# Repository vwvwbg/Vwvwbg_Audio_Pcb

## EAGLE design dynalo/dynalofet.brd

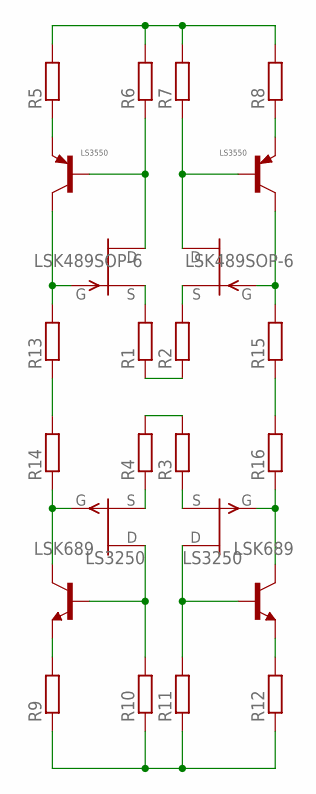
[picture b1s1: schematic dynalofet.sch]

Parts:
Q1: LS3250; SOT-23-6
Q2: LS3550; SOT-23-6
Q3: LSK489SOP-6; SOT-23-6
Q4: LSK689; SOT-23-6
R1, R2, R3, R4, R5, R6, R7, R8, R9, R10, R11, R12, R13, R14, R15, R16: R-EU_MELF0204W; MINI_MELF-0204W

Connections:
unnamed: Q2.3 (B), Q3.5 (D), R6.1
unnamed: Q2.4 (C), Q3.4 (G), R13.2
unnamed: Q2.1 (B), Q3.2 (D), R7.1
unnamed: Q2.6 (C), Q3.1 (G), R15.2
unnamed: Q1.4 (C), Q4.4 (G), R14.1
unnamed: Q1.3 (B), Q4.5 (D), R10.2
unnamed: Q1.1 (B), Q4.2 (D), R11.2
unnamed: Q1.6 (C), Q4.1 (G), R16.1
unnamed: Q4.3 (S), R3.1
unnamed: Q4.6 (S), R4.1
unnamed: Q3.6 (S), R1.2
unnamed: Q3.3 (S), R2.2
unnamed: R1.1, R2.1
unnamed: R3.2, R4.2
unnamed: R5.2, R6.2, R7.2, R8.2
unnamed: Q2.5 (E), R8.1
unnamed: Q2.2 (E), R5.1
unnamed: Q1.2 (E), R9.2
unnamed: Q1.5 (E), R12.2
unnamed: R9.1, R10.1, R11.1, R12.1
unnamed: R13.1, R14.2
unnamed: R15.1, R16.2

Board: 2 copper layers, 20 parts (0 on the bottom side), 22 nets, no tracks yet.

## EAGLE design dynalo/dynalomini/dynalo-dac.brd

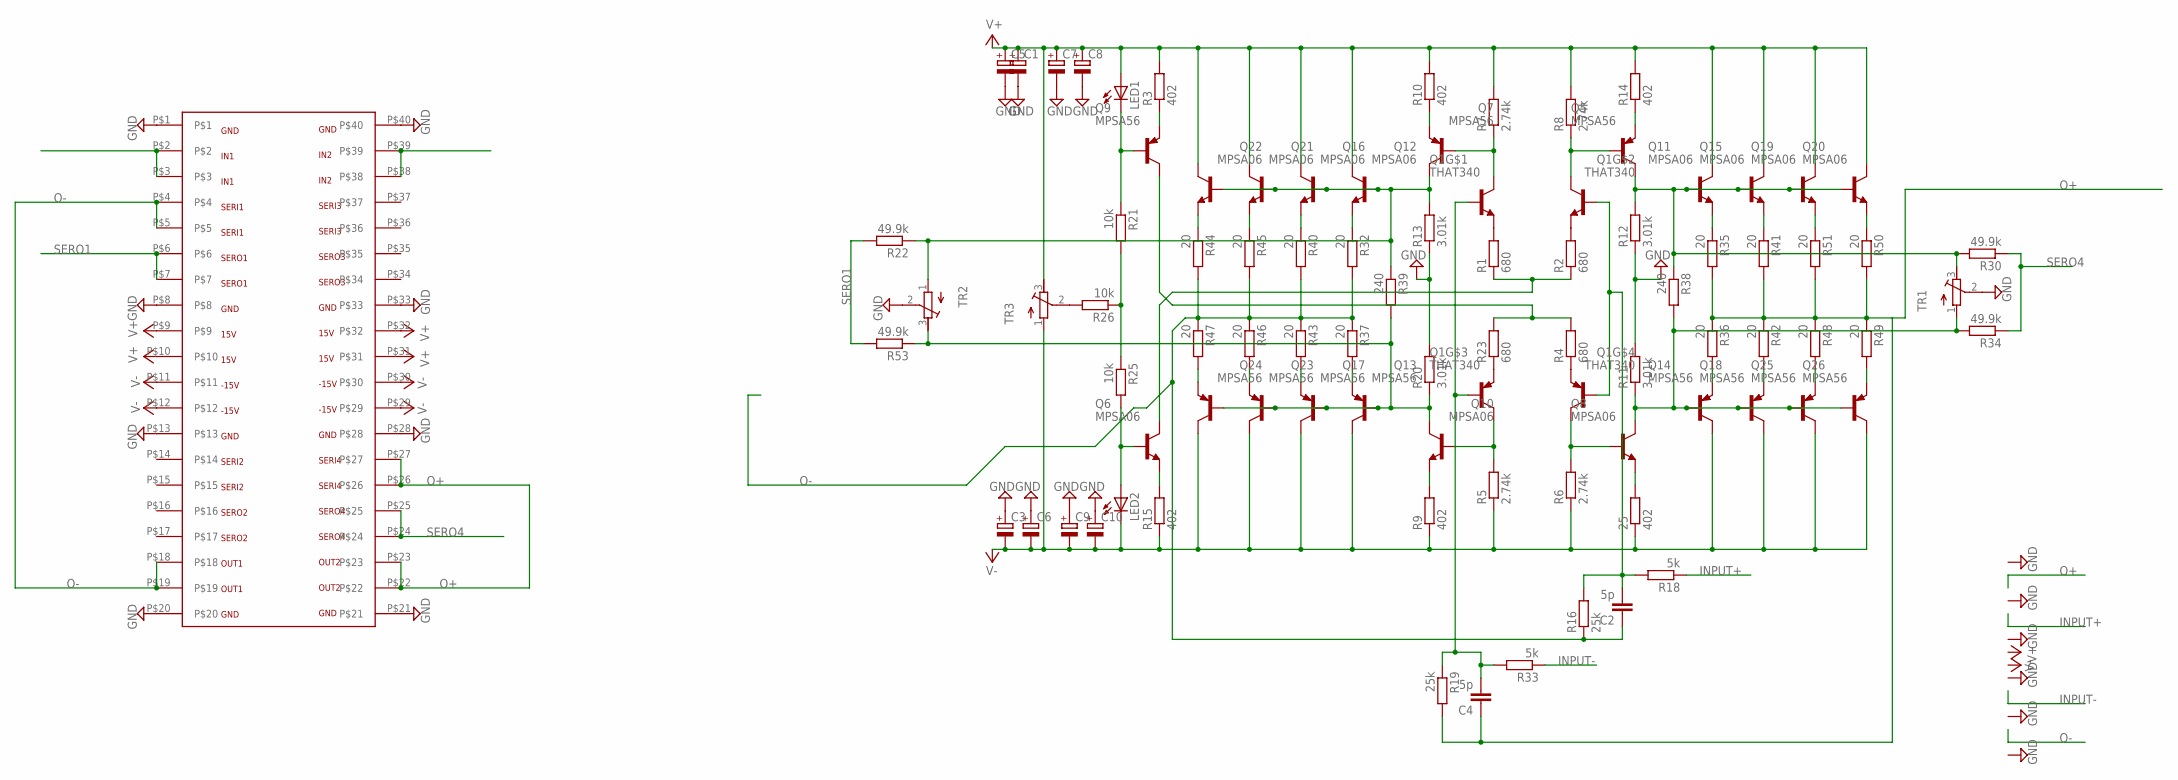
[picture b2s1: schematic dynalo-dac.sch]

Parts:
25: 402; MINI_MELF-0204W
C1, C3, C5, C6, C7, C8, C9, C10: CPOL-EUSP-CAP-CX; SP-CAP-CX
C2, C4: 5p; C0805
LED1, LED2: LED5MM
Q1: THAT340; DIP254P762X510-14
Q5, Q7, Q9, Q13, Q14, Q17, Q18, Q23, Q24, Q25, Q26: MPSA56; TO92-BCE
Q6, Q8, Q10, Q11, Q12, Q15, Q16, Q19, Q20, Q21, Q22: MPSA06; TO92-1
R1, R2, R4, R23: 680; MINI_MELF-0204W
R3, R9, R10, R14, R15: 402; MINI_MELF-0204W
R5, R6, R7, R8: 2.74k; MINI_MELF-0204W
R11, R12, R13, R20: 3.01k; MINI_MELF-0204W
R16, R19: 25k; MINI_MELF-0204W
R18, R33: 5k; MINI_MELF-0204W
R21, R25, R26: 10k; MINI_MELF-0204W
R22, R30, R34, R53: 49.9k; MINI_MELF-0204W
R32, R35, R36, R37, R40, R41, R42, R43, R44, R45, R46, R47, R48, R49, R50, R51: 20; MINI_MELF-0204W
R38, R39: 240; MINI_MELF-0204W
TR1, TR2, TR3: R-TRIMM3296W; RTRIM3296W
U$1: VDACA

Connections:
GND: C1.-, C3.+, C5.-, C6.+, C7.-, C8.-, C9.+, C10.+, R11.2, R12.1, R13.1, R20.2, TR1.2 (S), TR2.2 (S), U$1.P$1, U$1.P$8, U$1.P$13, U$1.P$20, U$1.P$21, U$1.P$28, U$1.P$33, U$1.P$40
INPUT+: R18.1, U$1.P$38, U$1.P$39
INPUT-: R33.1, U$1.P$2, U$1.P$3
unnamed: Q1.3 (E), R1.2
unnamed: Q1.12 (E), R2.2
unnamed: Q1.5 (E), R23.1
unnamed: Q1.10 (E), R4.1
unnamed: Q1.1 (C), Q7.C (B), R7.1
unnamed: Q1.14 (C), Q5.C (B), R8.1
unnamed: Q1.7 (C), Q10.2 (B), R5.2
unnamed: Q1.8 (C), Q8.2 (B), R6.2
unnamed: Q9.B (C), R4.2, R23.2
unnamed: Q6.3 (C), R1.1, R2.1
unnamed: Q10.1 (E), R9.2
unnamed: Q7.E, R10.1
unnamed: C4.2, Q1.2 (B), Q1.6 (B), R19.1, R33.2
unnamed: C2.2, Q1.9 (B), Q1.13 (B), R16.2, R18.2
unnamed: Q7.B (C), Q12.2 (B), Q16.2 (B), Q21.2 (B), Q22.2 (B), R13.2, R22.1, R39.1, TR2.1 (A)
unnamed: Q10.3 (C), Q13.C (B), Q17.C (B), Q23.C (B), Q24.C (B), R20.1, R39.2, R53.1, TR2.3 (E)
unnamed: Q11.1 (E), R35.1
unnamed: Q5.B (C), Q11.2 (B), Q15.2 (B), Q19.2 (B), Q20.2 (B), R12.2, R30.2, R38.1, TR1.3 (E)
unnamed: 25.2, Q8.1 (E)
unnamed: Q14.E, R36.2
unnamed: Q5.E, R14.1
unnamed: Q9.E, R3.1
unnamed: Q6.1 (E), R15.2
unnamed: Q18.E, R42.2
unnamed: Q15.1 (E), R41.1
unnamed: Q19.1 (E), R51.1
unnamed: Q20.1 (E), R50.1
unnamed: Q25.E, R48.2
unnamed: Q8.3 (C), Q14.C (B), Q18.C (B), Q25.C (B), Q26.C (B), R11.1, R34.2, R38.2, TR1.1 (A)
unnamed: Q26.E, R49.2
unnamed: R26.2, TR3.2 (S)
unnamed: R21.2, R25.1, R26.1
unnamed: Q22.1 (E), R44.1
unnamed: Q21.1 (E), R45.1
unnamed: Q16.1 (E), R40.1
unnamed: Q12.1 (E), R32.1
unnamed: Q24.E, R47.2
unnamed: Q23.E, R46.2
unnamed: Q17.E, R43.2
unnamed: Q13.E, R37.2
unnamed: LED2.A, Q6.2 (B), R25.2
unnamed: LED1.K (C), Q9.C (B), R21.1
O+: C4.1, R19.2, R35.2, R36.1, R41.2, R42.1, R48.1, R49.1, R50.2, R51.2, U$1.P$22, U$1.P$23, U$1.P$26, U$1.P$27
O-: C2.1, R16.1, R32.2, R37.1, R40.2, R43.1, R44.2, R45.2, R46.1, R47.1, U$1.P$4, U$1.P$5, U$1.P$18, U$1.P$19
SERO1: R22.2, R53.2, U$1.P$6, U$1.P$7
SERO4: R30.1, R34.1, U$1.P$24, U$1.P$25
V+: C1.+, C5.+, C7.+, C8.+, LED1.A, Q11.3 (C), Q12.3 (C), Q15.3 (C), Q16.3 (C), Q19.3 (C), Q20.3 (C), Q21.3 (C), Q22.3 (C), R3.2, R7.2, R8.2, R10.2, R14.2, TR3.3 (E), U$1.P$9, U$1.P$10, U$1.P$31, U$1.P$32
V-: 25.1, C3.-, C6.-, C9.-, C10.-, LED2.K (C), Q13.B (C), Q14.B (C), Q17.B (C), Q18.B (C), Q23.B (C), Q24.B (C), Q25.B (C), Q26.B (C), R5.1, R6.1, R9.1, R15.1, TR3.1 (A), U$1.P$11, U$1.P$12, U$1.P$29, U$1.P$30

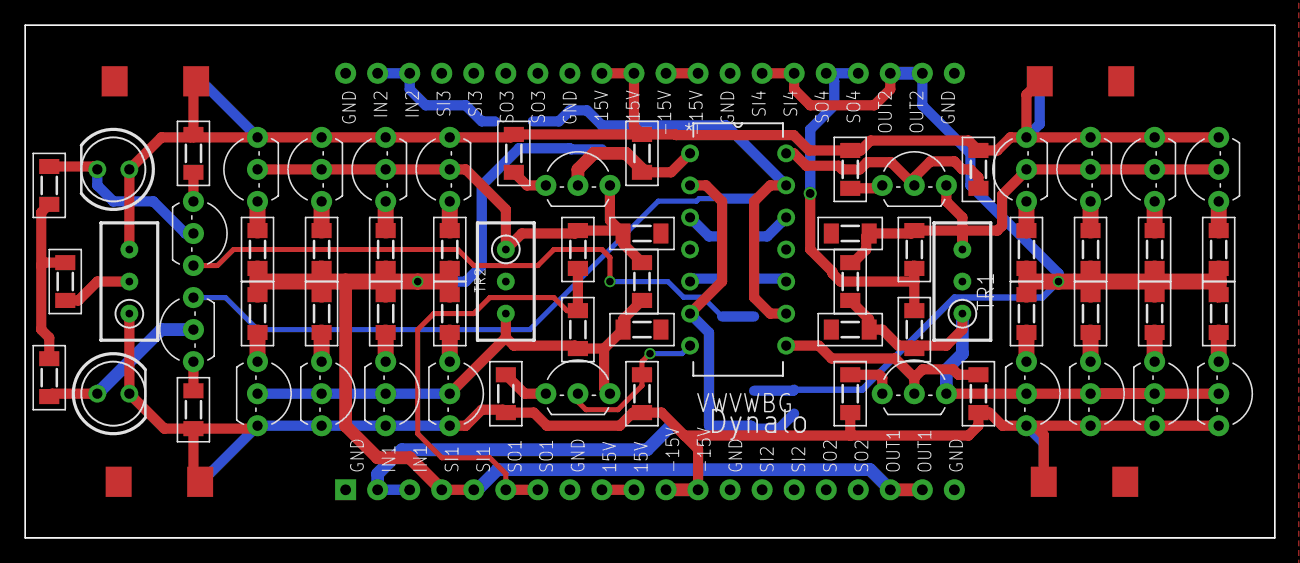
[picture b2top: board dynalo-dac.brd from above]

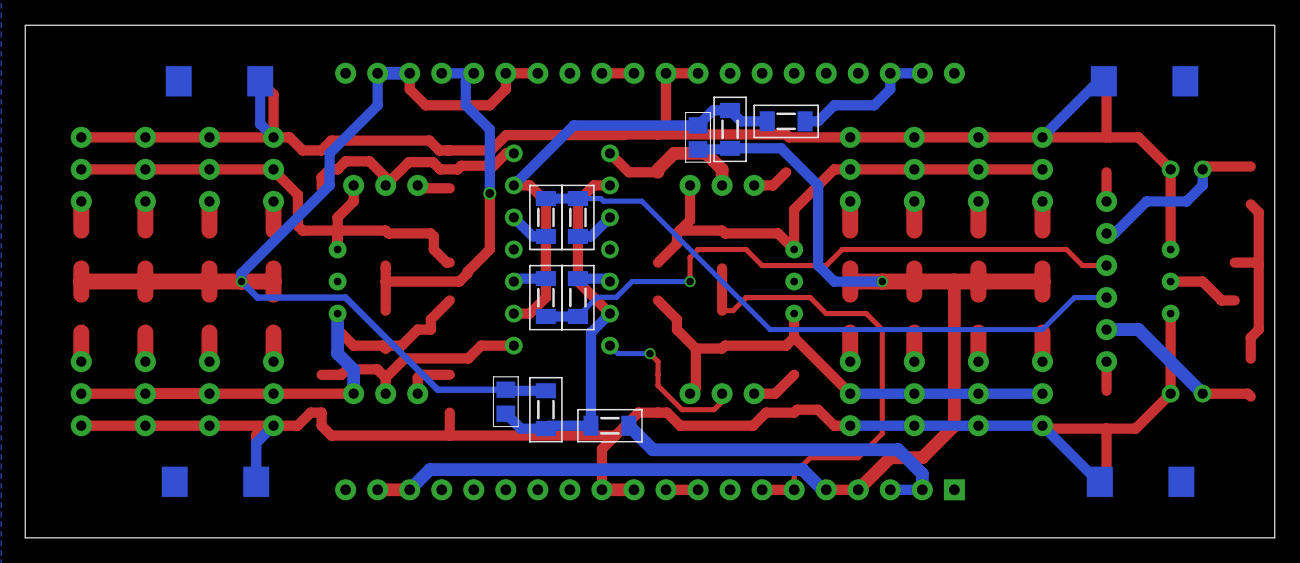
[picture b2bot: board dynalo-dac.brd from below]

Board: 2 copper layers, 99.1 x 40.6 mm, 86 parts (14 on the bottom side), 51 nets.

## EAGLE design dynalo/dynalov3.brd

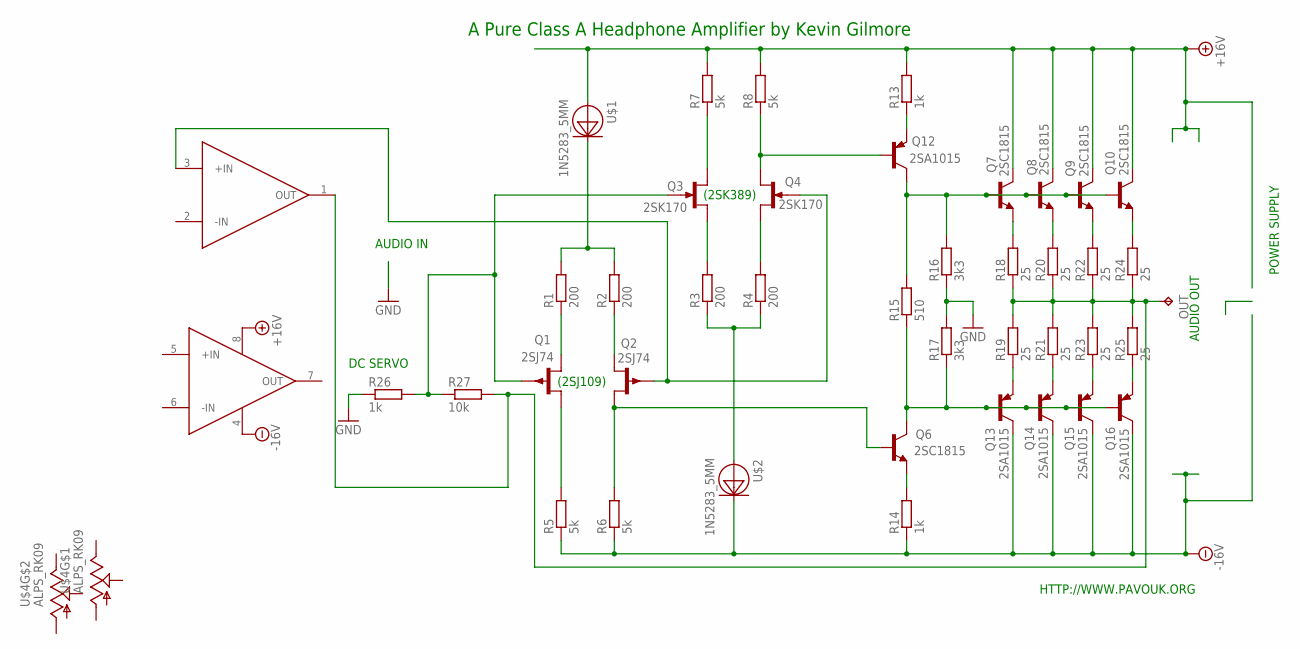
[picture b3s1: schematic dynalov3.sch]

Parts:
OUT: TPPAD1-20; P1-20
Q1, Q2: 2SJ74; TO92F
Q3, Q4: 2SK170; TO92F
Q6, Q7, Q8, Q9, Q10: 2SC1815; TO92-ECB
Q12, Q13, Q14, Q15, Q16: 2SA1015; TO92-ECB
R1, R2, R3, R4: 200; MINI_MELF-0204W
R5, R6, R7, R8: 5k; MINI_MELF-0204W
R13, R14, R26: 1k; MINI_MELF-0204W
R15: 510; MINI_MELF-0204W
R16, R17: 3k3; MINI_MELF-0204W
R18, R19, R20, R21, R22, R23, R24, R25: 25; MINI_MELF-0204W
R27: 10k; MINI_MELF-0204W
U$1, U$2: 1N5283_5MM; DO-35-2
U$3: LME49720; DIL08
U$4: ALPS_RK09; RK09

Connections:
+15V: Q7.C, Q8.C, Q9.C, Q10.C, R7.2, R8.2, R13.2, U$1.ANODE, U$3.8 (V+)
-15V: Q13.C, Q14.C, Q15.C, Q16.C, R5.1, R6.1, R14.1, U$2.CATHODE, U$3.4 (V-)
GND: R16.1, R17.2, R26.1
unnamed: OUT.TP, R18.1, R19.2, R20.1, R21.2, R22.1, R23.2, R24.1, R25.2, R27.2, U$3.1 (OUT)
unnamed: Q7.E, R18.2
unnamed: Q8.E, R20.2
unnamed: Q9.E, R22.2
unnamed: Q10.E, R24.2
unnamed: Q13.E, R19.1
unnamed: Q14.E, R21.1
unnamed: Q15.E, R23.1
unnamed: Q16.E, R25.1
unnamed: Q7.B, Q8.B, Q9.B, Q10.B, Q12.C, R15.2, R16.2
unnamed: Q6.C, Q13.B, Q14.B, Q15.B, Q16.B, R15.1, R17.1
unnamed: Q12.E, R13.1
unnamed: Q6.E, R14.2
unnamed: R3.1, R4.1, U$2.ANODE
unnamed: Q3.D, R7.1
unnamed: Q3.S, R3.2
unnamed: Q4.D, R4.2
unnamed: Q4.S, Q12.B, R8.1
unnamed: Q1.D, R1.1
unnamed: Q2.D, Q6.B, R6.2
unnamed: Q2.S, R2.1
unnamed: Q1.S, R5.2
unnamed: R1.2, R2.2, U$1.CATHODE
unnamed: Q1.G, Q3.G, R26.2, R27.1
unnamed: Q2.G, Q4.G, U$3.3 (+IN)

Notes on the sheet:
A Pure Class A Headphone Amplifier by Kevin Gilmore
HTTP://WWW.PAVOUK.ORG
DC SERVO
AUDIO IN
AUDIO OUT
(2SK389)
(2SJ109)
POWER SUPPLY

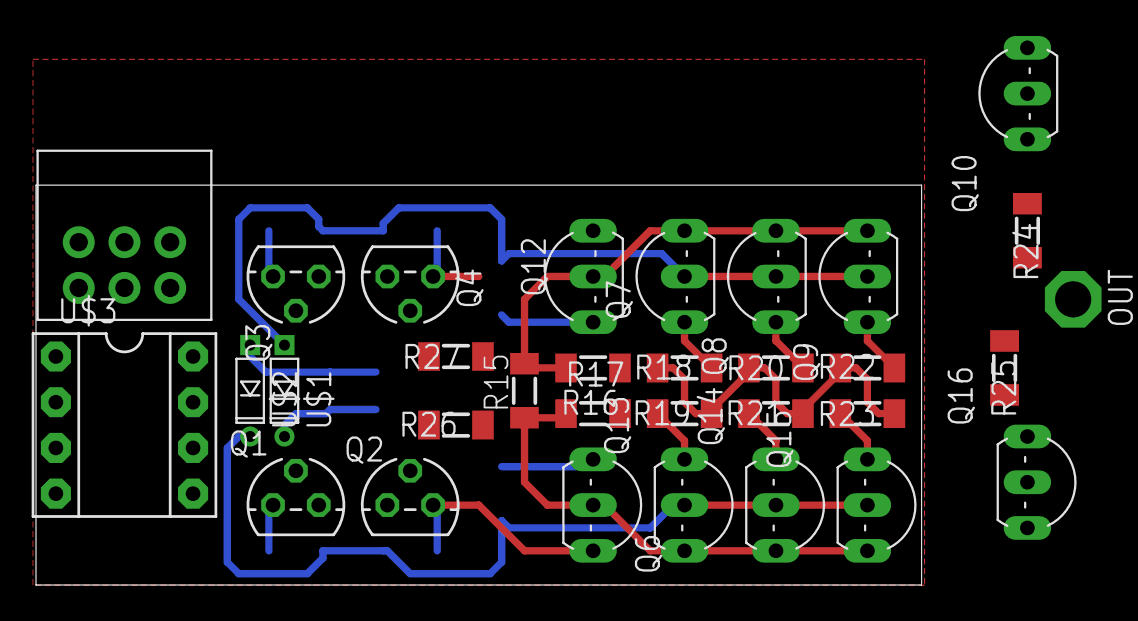
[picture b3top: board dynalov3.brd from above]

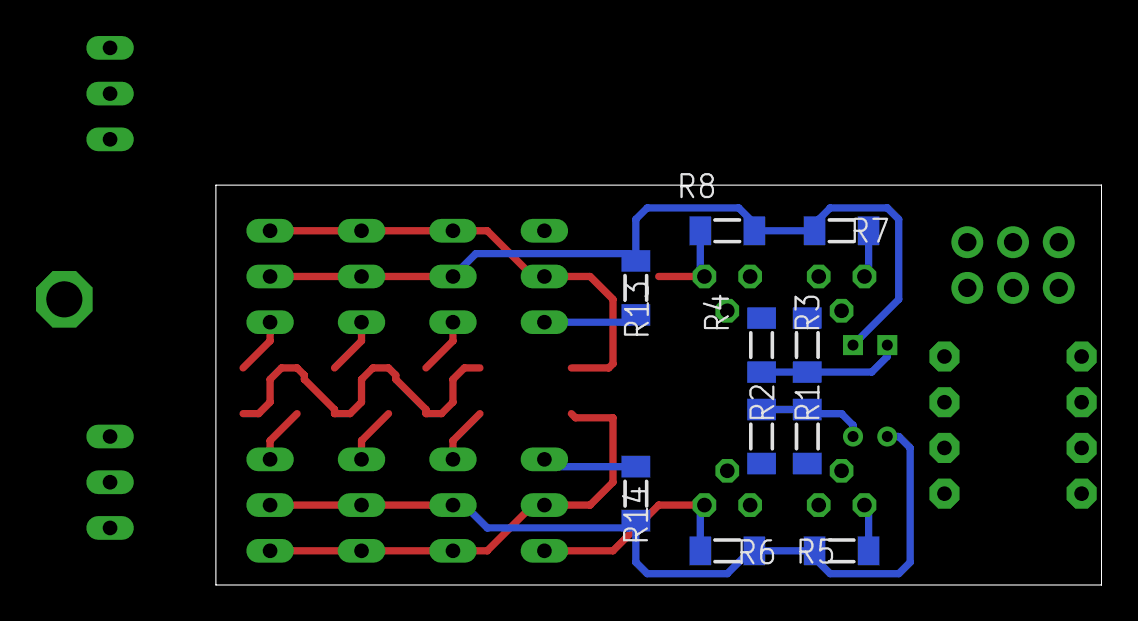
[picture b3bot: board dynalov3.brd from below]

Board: 2 copper layers, 49.2 x 22.2 mm, 42 parts (10 on the bottom side), 28 nets.

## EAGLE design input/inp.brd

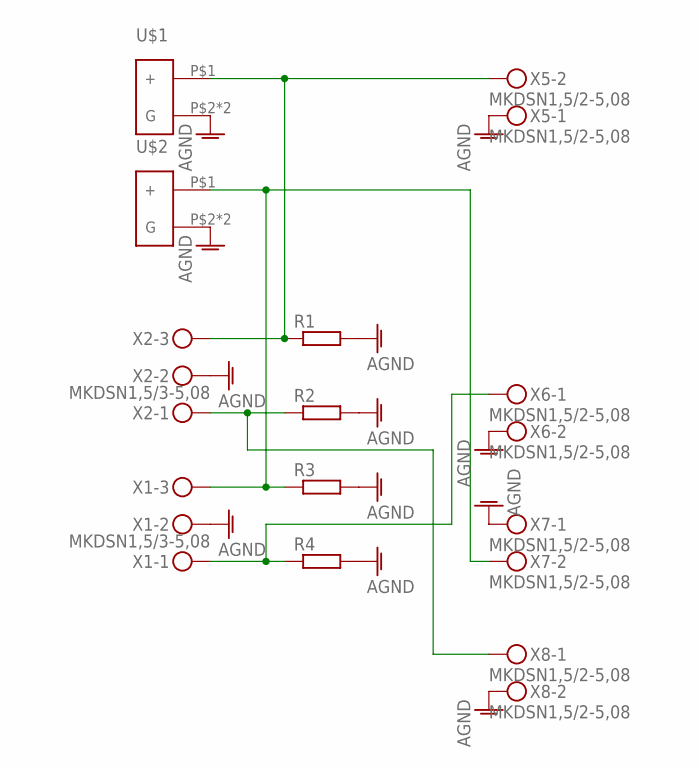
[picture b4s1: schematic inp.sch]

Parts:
R1, R2, R3, R4: R-EU_MELF0204W; MINI_MELF-0204W
U$1, U$2: MSRCA
X1, X2: MKDSN1,5/3-5,08
X5, X6, X7, X8: MKDSN1,5/2-5,08

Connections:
AGND: R1.2, R2.2, R3.2, R4.2, U$1.P$2 (G), U$1.P$3 (G), U$2.P$2 (G), U$2.P$3 (G), X1.2, X2.2, X5.1, X6.2, X7.1, X8.2
unnamed: R1.1, U$1.P$1 (+), X2.3, X5.2
unnamed: R3.1, U$2.P$1 (+), X1.3, X7.2
unnamed: R2.1, X2.1, X8.1
unnamed: R4.1, X1.1, X6.1

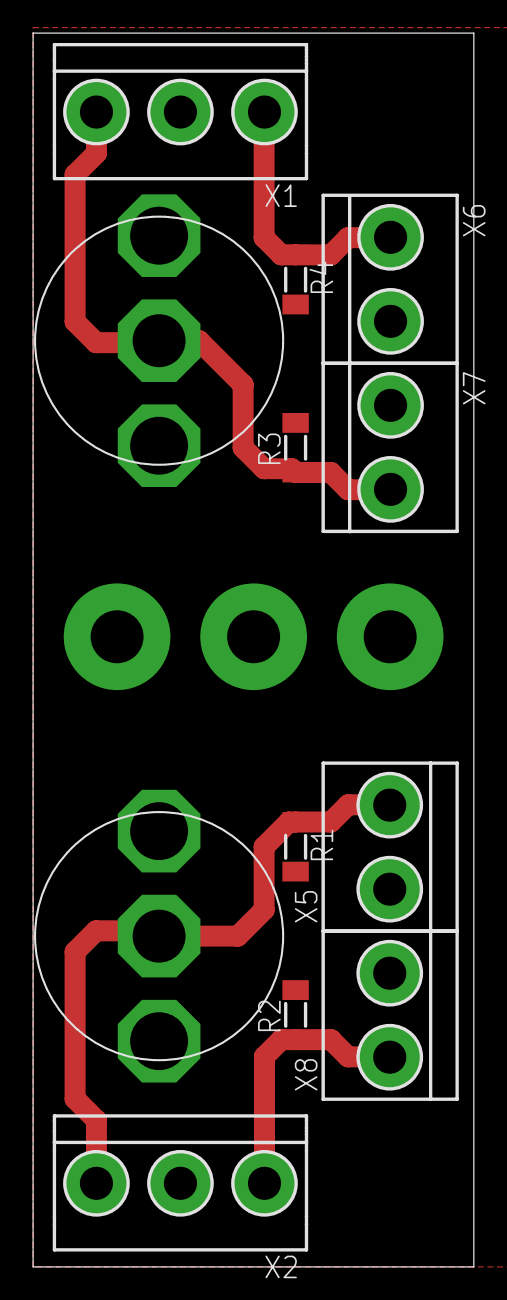
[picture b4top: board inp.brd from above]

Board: 2 copper layers, 26.6 x 74.6 mm, 12 parts (0 on the bottom side), 5 nets.

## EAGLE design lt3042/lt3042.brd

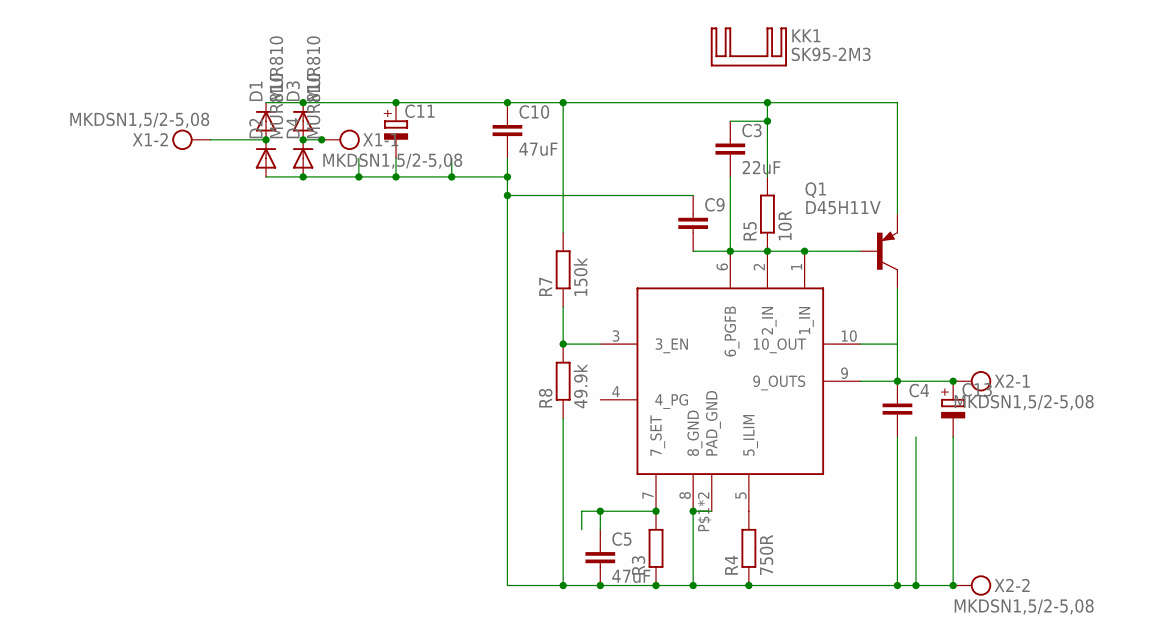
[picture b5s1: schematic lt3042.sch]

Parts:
C3: 22uF; C1210
C4, C9: C-EUC1206; C1206
C5, C10: 47uF; C1210
C11: CPOL-EUE7.5-18; E7,5-18
C13: CPOL-EUE5-10.5; E5-10,5
D1, D2, D3, D4: MUR810; TO220ACS
KK1: SK95-2M3
Q1: D45H11V; TO220V
R3: R-EU_R1206; R1206
R4: 750R; R1206
R5: 10R; R1206
R7: 150k; R1206
R8: 49.9k; R1206
U$1: LT3042; MSOP-10
X1, X2: MKDSN1,5/2-5,08

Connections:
EN: R7.1, R8.2, U$1.3 (3_EN)
GND: C4.2, C5.2, C9.1, C10.2, C11.-, C13.-, D2.A, D4.A, R3.1, R4.1, R8.1, U$1.8 (8_GND), U$1.P$1 (PAD_GND), U$1.P$2 (PAD_GND), X2.2
ILIM: R4.2, U$1.5 (5_ILIM)
unnamed: D1.A, D2.C, X1.2
unnamed: C3.1, C10.1, C11.+, D1.C, D3.C, Q1.3 (E), R5.2, R7.2
unnamed: D3.A, D4.C, X1.1
SET: C5.1, R3.2, U$1.7 (7_SET)
VIN: C3.2, C9.2, Q1.1 (B), R5.1, U$1.1 (1_IN), U$1.2 (2_IN), U$1.6 (6_PGFB)
VOUT: C4.1, C13.+, Q1.2 (C), U$1.9 (9_OUTS), U$1.10 (10_OUT), X2.1

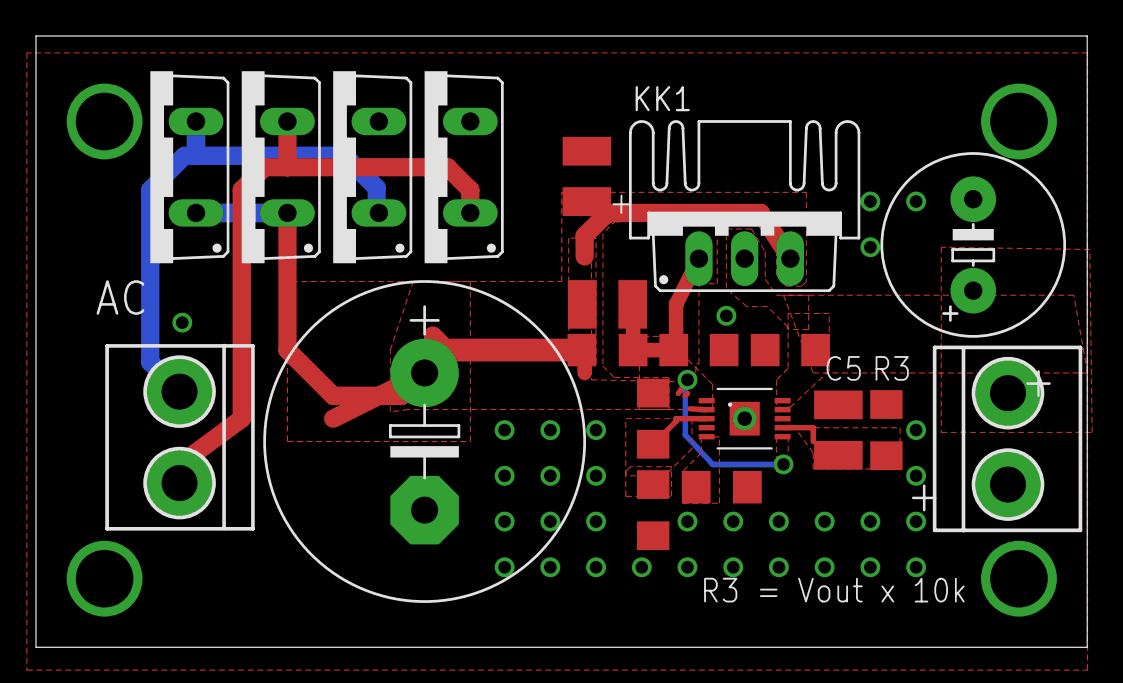
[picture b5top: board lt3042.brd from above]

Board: 2 copper layers, 58.4 x 34.0 mm, 21 parts (0 on the bottom side), 9 nets.

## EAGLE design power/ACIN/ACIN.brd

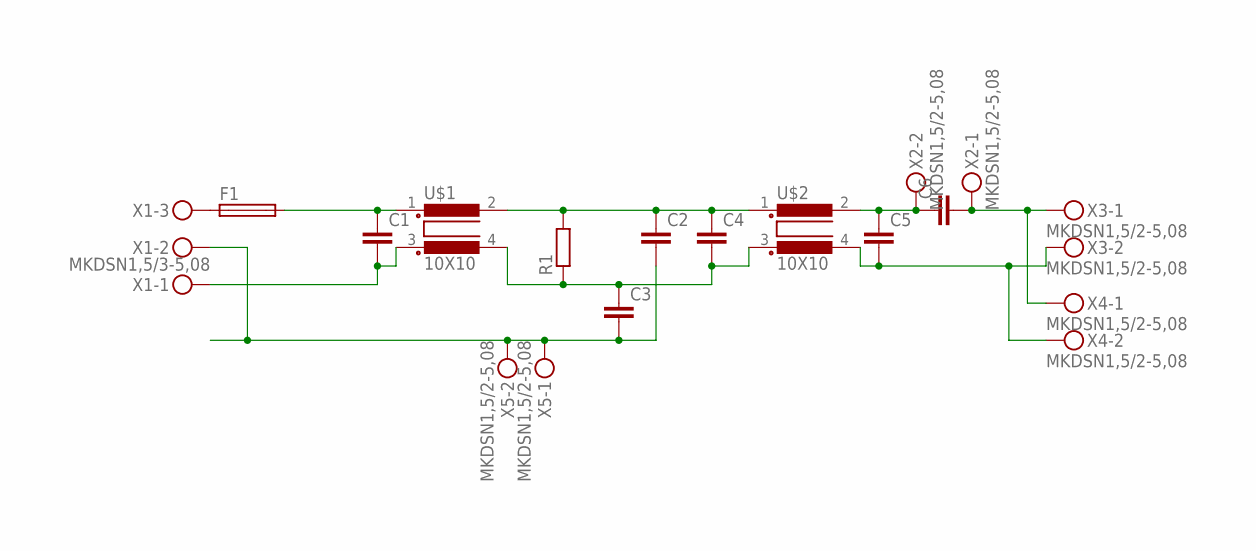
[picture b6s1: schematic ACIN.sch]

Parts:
C1, C4, C5: C-EU225-087X268; C225-087X268
C2, C3: C-EU102-054X133; C102-054X133
C6: C-EU075-042X103; C075-042X103
F1: SH22,5A
R1: R-EU_0309/12; 0309/12
U$1, U$2: 10X10
X1: MKDSN1,5/3-5,08
X2, X3, X4, X5: MKDSN1,5/2-5,08

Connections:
unnamed: F1.1, X1.3
unnamed: C1.1, F1.2, U$1.1
unnamed: C5.1, C6.1, U$2.2, X2.2
unnamed: C2.1, C4.1, R1.2, U$1.2, U$2.1
unnamed: C3.1, C4.2, R1.1, U$1.4, U$2.3
unnamed: C2.2, C3.2, X1.2, X5.1, X5.2
unnamed: C6.2, X2.1, X3.1, X4.1
unnamed: C5.2, U$2.4, X3.2, X4.2
unnamed: C1.2, U$1.3, X1.1

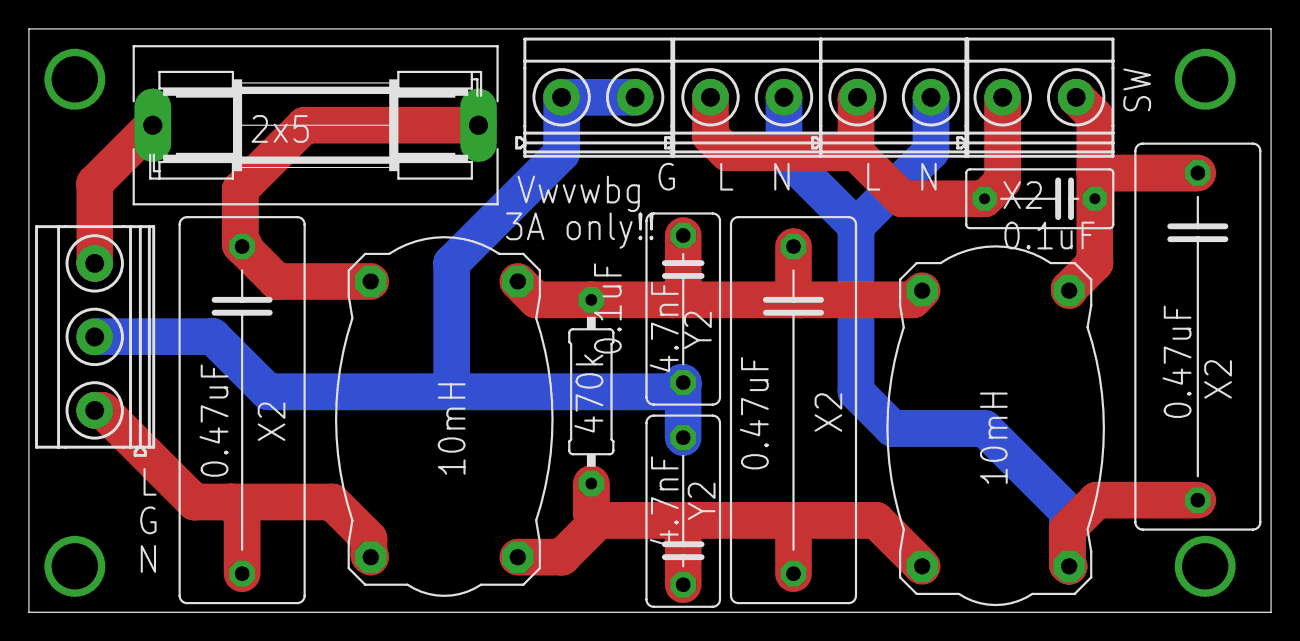
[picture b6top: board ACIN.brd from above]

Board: 2 copper layers, 85.8 x 40.3 mm, 15 parts (0 on the bottom side), 9 nets.
